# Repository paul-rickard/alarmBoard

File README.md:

# alarmBoard
Custom Alarm PCB - in Kicad

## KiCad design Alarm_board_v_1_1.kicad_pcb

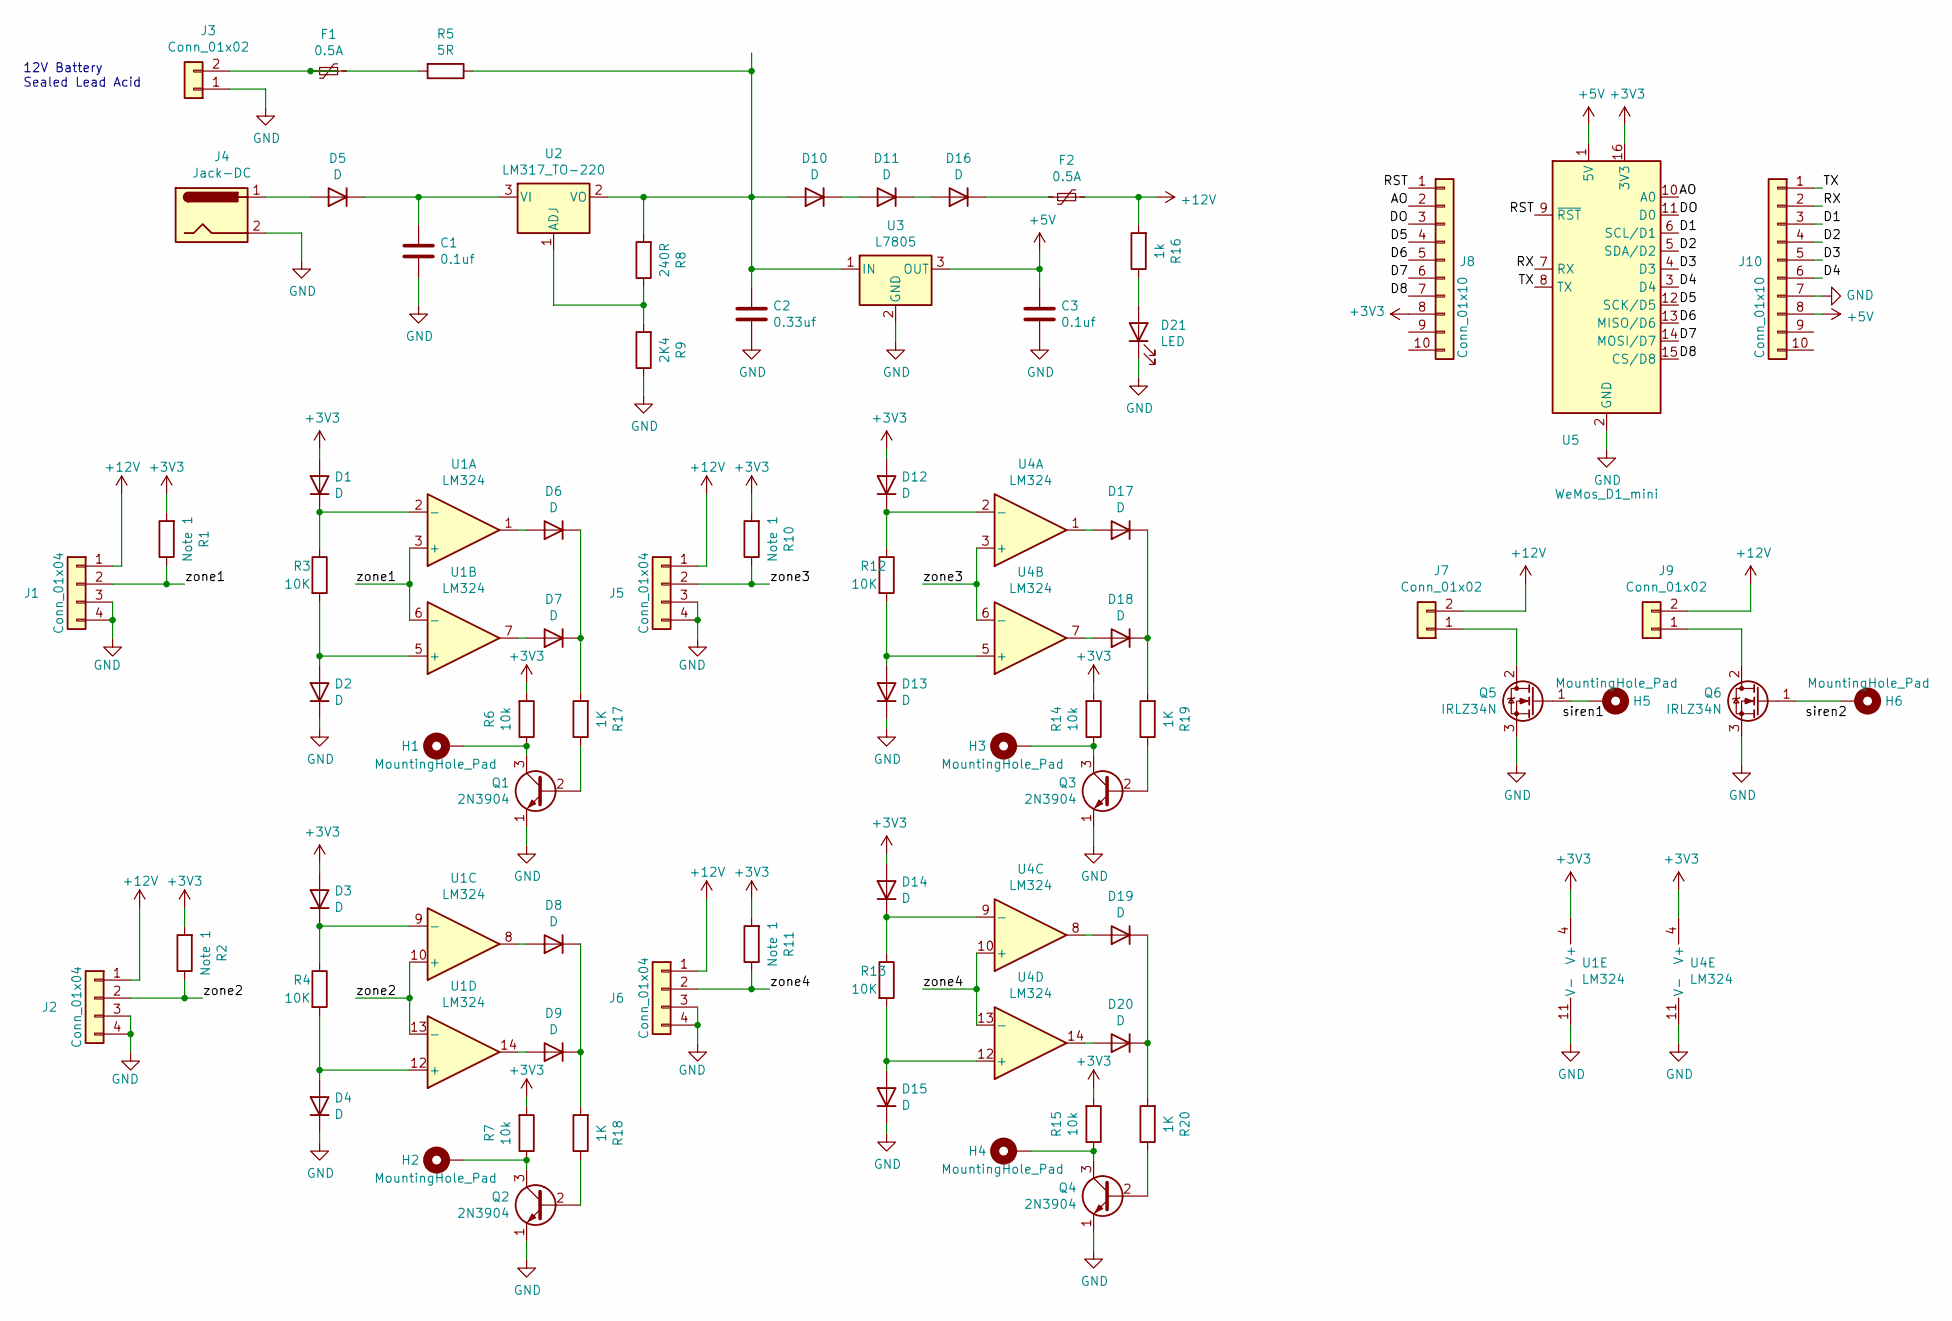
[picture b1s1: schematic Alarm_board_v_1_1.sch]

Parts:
C1, C3: 0.1uf; CP_Radial_Tantal_D4.5mm_P5.00mm
C2: 0.33uf; CP_Radial_Tantal_D4.5mm_P2.50mm
D1, D2, D3, D4, D5, D6, D7, D8, D9, D10, D11, D12, D13, D14, D15, D16, D17, D18, D19, D20: D; D_A-405_P10.16mm_Horizontal
D21: LED; LED_D3.0mm
F1, F2: 0.5A; C_Radial_D10.0mm_H12.5mm_P5.00mm
H1, H2, H3, H4, H5, H6: MountingHole_Pad; Pin_D1.0mm_L10.0mm
J1, J2, J5, J6: Conn_01x04; TerminalBlock_Phoenix_PT-1,5-4-5.0-H_1x04_P5.00mm_Horizontal
J3, J7, J9: Conn_01x02; TerminalBlock_Phoenix_PT-1,5-2-5.0-H_1x02_P5.00mm_Horizontal
J4: Jack-DC; BarrelJack_Wuerth_6941xx301002
J8, J10: Conn_01x10; PinHeader_1x10_P2.54mm_Vertical
Q1, Q2, Q3, Q4: 2N3904; TO-92_Inline
Q5, Q6: IRLZ34N; TO-220-3_Horizontal_TabDown
R1, R2, R10, R11: Note 1; R_Axial_DIN0204_L3.6mm_D1.6mm_P5.08mm_Horizontal
R3, R4, R12, R13: 10K; R_Axial_DIN0204_L3.6mm_D1.6mm_P5.08mm_Horizontal
R5: 5R; R_Axial_Power_L20.0mm_W6.4mm_P30.48mm
R6, R7, R14, R15: 10k; R_Axial_DIN0204_L3.6mm_D1.6mm_P5.08mm_Horizontal
R8: 240R; R_Axial_DIN0204_L3.6mm_D1.6mm_P5.08mm_Horizontal
R9: 2K4; R_Axial_DIN0204_L3.6mm_D1.6mm_P5.08mm_Horizontal
R16: 1k; R_Axial_DIN0204_L3.6mm_D1.6mm_P5.08mm_Horizontal
R17, R18, R19, R20: 1K; R_Axial_DIN0204_L3.6mm_D1.6mm_P5.08mm_Horizontal
U1, U4: LM324; DIP-14_W7.62mm_Socket
U2: LM317_TO-220; TO-220-3_Horizontal_TabDown
U3: L7805; TO-126-3_Horizontal_TabDown
U5: WeMos_D1_mini; wemos-d1-mini-with-pin-header

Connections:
+3V3: D1.2 (A), D3.2 (A), D12.2 (A), D14.2 (A), J8.8, R1.2, R2.2, R6.2, R7.2, R10.2, R11.2, R14.2, R15.2, U1.4 (V+), U4.4 (V+), U5.16 (3V3); also elsewhere on the board
+5V: C3.1, J10.8, U3.3 (OUT), U5.1 (5V); also elsewhere on the board
+12V: F2.1, J1.1, J2.1, J5.1, J6.1, J7.2, J9.2, R16.2
/AO: J8.2, U5.10 (A0); also elsewhere on the board
/D1: J10.3, U5.6 (SCL/D1); also elsewhere on the board
/D2: J10.4, U5.5 (SDA/D2); also elsewhere on the board
/D3: J10.5, U5.4 (D3); also elsewhere on the board
/D4: J10.6, U5.3 (D4); also elsewhere on the board
/D5: J8.4, U5.12 (SCK/D5); also elsewhere on the board
/D6: J8.5, U5.13 (MISO/D6); also elsewhere on the board
/D7: J8.6, U5.14 (MOSI/D7); also elsewhere on the board
/D8: J8.7, U5.15 (CS/D8); also elsewhere on the board
/DO: J8.3, U5.11 (D0); also elsewhere on the board
/RST: J8.1, U5.9 (~RST); also elsewhere on the board
/RX: J10.2, U5.7 (RX); also elsewhere on the board
/TX: J10.1, U5.8 (TX); also elsewhere on the board
/zone1: J1.2, R1.1, U1.3 (+), U1.6 (-)
/zone2: J2.2, R2.1, U1.10 (+), U1.13 (-)
/zone3: J5.2, R10.1, U4.3 (+), U4.6 (-)
/zone4: J6.2, R11.1, U4.10 (+), U4.13 (-)
GND: C1.2, C2.2, C3.2, D2.1 (K), D4.1 (K), D13.1 (K), D15.1 (K), D21.1 (K), J1.3, J1.4, J2.3, J2.4, J3.1, J4.2, J5.3, J5.4, J6.3, J6.4, J10.7, Q1.1 (E), Q2.1 (E), Q3.1 (E), Q4.1 (E), Q5.3 (S), Q6.3 (S), R9.1, U1.11 (V-), U3.2 (GND), U4.11 (V-), U5.2 (GND); also elsewhere on the board
unnamed: C1.1, D5.1 (K), U2.3 (VI)
unnamed: C2.1, D10.2 (A), R5.1, R8.2, U2.2 (VO), U3.1 (IN)
unnamed: D1.1 (K), R3.1, U1.2 (-)
unnamed: D2.2 (A), R3.2, U1.5 (+)
unnamed: D3.1 (K), R4.1, U1.9 (-)
unnamed: D4.2 (A), R4.2, U1.12 (+)
unnamed: D5.2 (A), J4.1
unnamed: D6.1 (K), D7.1 (K), R17.2
unnamed: D6.2 (A), U1.1
unnamed: D7.2 (A), U1.7
unnamed: D8.1 (K), D9.1 (K), R18.2
unnamed: D8.2 (A), U1.8
unnamed: D9.2 (A), U1.14
unnamed: D10.1 (K), D11.2 (A)
unnamed: D11.1 (K), D16.2 (A)
unnamed: D12.1 (K), R12.1, U4.2 (-)
unnamed: D13.2 (A), R12.2, U4.5 (+)
unnamed: D14.1 (K), R13.1, U4.9 (-)
unnamed: D15.2 (A), R13.2, U4.12 (+)
unnamed: D16.1 (K), F2.2
unnamed: D17.1 (K), D18.1 (K), R19.2
unnamed: D17.2 (A), U4.1
unnamed: D18.2 (A), U4.7
unnamed: D19.1 (K), D20.1 (K), R20.2
unnamed: D19.2 (A), U4.8
unnamed: D20.2 (A), U4.14
unnamed: D21.2 (A), R16.1
unnamed: F1.1, R5.2
unnamed: F1.2, J3.2
unnamed: H1.1, Q1.3 (C), R6.1
unnamed: H2.1, Q2.3 (C), R7.1
unnamed: H3.1, Q3.3 (C), R14.1
unnamed: H4.1, Q4.3 (C), R15.1
unnamed: H5.1, Q5.1 (G)
unnamed: H6.1, Q6.1 (G)
unnamed: J7.1, Q5.2 (D)
unnamed: J9.1, Q6.2 (D)
unnamed: Q1.2 (B), R17.1
unnamed: Q2.2 (B), R18.1
unnamed: Q3.2 (B), R19.1
unnamed: Q4.2 (B), R20.1
unnamed: R8.1, R9.2, U2.1 (ADJ)

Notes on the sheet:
12V Battery Sealed Lead Acid

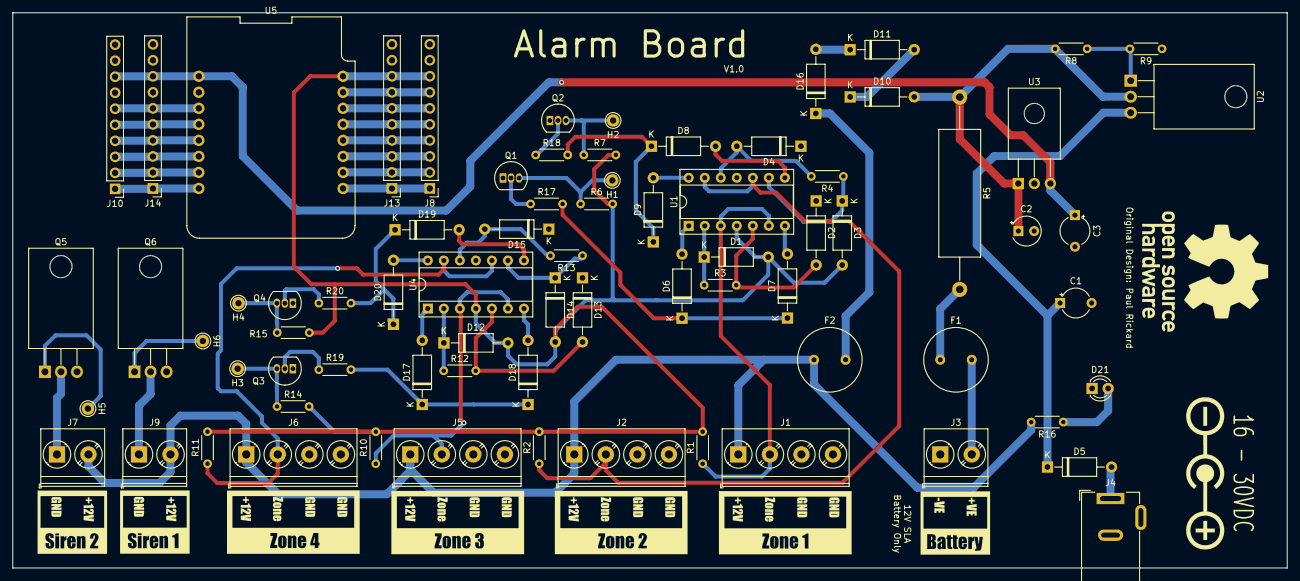
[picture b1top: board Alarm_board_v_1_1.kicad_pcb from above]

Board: 2 copper layers, 202.0 x 88.0 mm, 75 parts (0 on the bottom side), 63 nets.

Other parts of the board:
J13, J14: Conn_01x10_MountingPin; PinHeader_1x10_P2.54mm_Vertical

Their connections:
+3V3: J13.8; also elsewhere on the board
+5V: J14.8; also elsewhere on the board
/AO: J13.2; also elsewhere on the board
/D1: J14.3; also elsewhere on the board
/D2: J14.4; also elsewhere on the board
/D3: J14.5; also elsewhere on the board
/D4: J14.6; also elsewhere on the board
/D5: J13.4; also elsewhere on the board
/D6: J13.5; also elsewhere on the board
/D7: J13.6; also elsewhere on the board
/D8: J13.7; also elsewhere on the board
/DO: J13.3; also elsewhere on the board
/RST: J13.1; also elsewhere on the board
/RX: J14.2; also elsewhere on the board
/TX: J14.1; also elsewhere on the board
GND: J14.7; also elsewhere on the board
